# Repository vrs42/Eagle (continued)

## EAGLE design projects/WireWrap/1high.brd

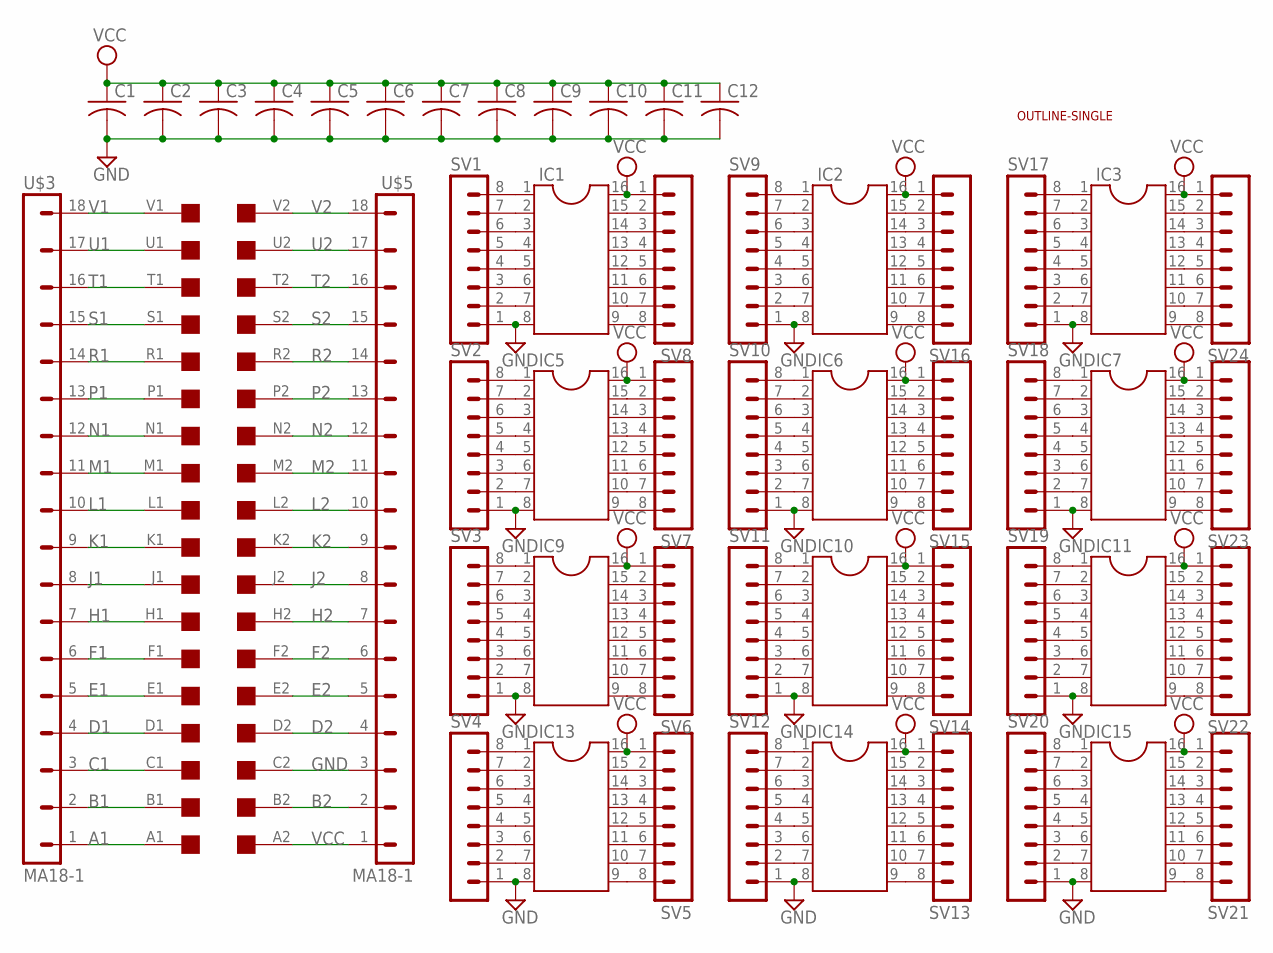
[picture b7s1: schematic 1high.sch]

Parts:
C1, C2, C3, C4, C5, C6, C7, C8, C9, C10, C11, C12: C-US050-025X075; C050-025X075
IC1, IC2, IC3, IC5, IC6, IC7, IC9, IC10, IC11, IC13, IC14, IC15: DIL16
SV1, SV2, SV3, SV4, SV5, SV6, SV7, SV8, SV9, SV10, SV11, SV12, SV13, SV14, SV15, SV16, SV17, SV18, SV19, SV20, SV21, SV22, SV23, SV24: MA08-1
U$2: OUTLINE-SINGLE; SINGLE
U$3, U$5: MA18-1
U$4: EDGE-2CONNECTOR; EDGE-CON2

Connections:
A1: U$3.1, U$4.A1
B1: U$3.2, U$4.B1
B2: U$4.B2, U$5.2
C1: U$3.3, U$4.C1
D1: U$3.4, U$4.D1
D2: U$4.D2, U$5.4
E1: U$3.5, U$4.E1
E2: U$4.E2, U$5.5
F1: U$3.6, U$4.F1
F2: U$4.F2, U$5.6
GND: C1.2, C2.2, C3.2, C4.2, C5.2, C6.2, C7.2, C8.2, C9.2, C10.2, C11.2, C12.2, IC1.8, IC2.8, IC3.8, IC5.8, IC6.8, IC7.8, IC9.8, IC10.8, IC11.8, IC13.8, IC14.8, IC15.8, SV1.1, SV2.1, SV3.1, SV4.1, SV9.1, SV10.1, SV11.1, SV12.1, SV17.1, SV18.1, SV19.1, SV20.1, U$4.C2, U$5.3
H1: U$3.7, U$4.H1
H2: U$4.H2, U$5.7
J1: U$3.8, U$4.J1
J2: U$4.J2, U$5.8
K1: U$3.9, U$4.K1
K2: U$4.K2, U$5.9
L1: U$3.10, U$4.L1
L2: U$4.L2, U$5.10
M1: U$3.11, U$4.M1
M2: U$4.M2, U$5.11
N1: U$3.12, U$4.N1
N2: U$4.N2, U$5.12
unnamed: IC1.7, SV1.2
unnamed: IC1.6, SV1.3
unnamed: IC1.5, SV1.4
unnamed: IC1.4, SV1.5
unnamed: IC1.3, SV1.6
unnamed: IC1.2, SV1.7
unnamed: IC1.1, SV1.8
unnamed: IC5.7, SV2.2
unnamed: IC5.6, SV2.3
unnamed: IC5.5, SV2.4
unnamed: IC5.4, SV2.5
unnamed: IC5.3, SV2.6
unnamed: IC5.2, SV2.7
unnamed: IC5.1, SV2.8
unnamed: IC9.7, SV3.2
unnamed: IC9.6, SV3.3
unnamed: IC9.5, SV3.4
unnamed: IC9.4, SV3.5
unnamed: IC9.3, SV3.6
unnamed: IC9.2, SV3.7
unnamed: IC9.1, SV3.8
unnamed: IC13.7, SV4.2
unnamed: IC13.6, SV4.3
unnamed: IC13.5, SV4.4
unnamed: IC13.4, SV4.5
unnamed: IC13.3, SV4.6
unnamed: IC13.2, SV4.7
unnamed: IC13.1, SV4.8
unnamed: IC2.1, SV9.8
unnamed: IC2.2, SV9.7
unnamed: IC2.3, SV9.6
unnamed: IC2.4, SV9.5
unnamed: IC2.5, SV9.4
unnamed: IC2.6, SV9.3
unnamed: IC2.7, SV9.2
unnamed: IC6.1, SV10.8
unnamed: IC6.2, SV10.7
unnamed: IC6.3, SV10.6
unnamed: IC6.4, SV10.5
unnamed: IC6.5, SV10.4
unnamed: IC6.6, SV10.3
unnamed: IC6.7, SV10.2
unnamed: IC10.1, SV11.8
unnamed: IC10.2, SV11.7
unnamed: IC10.3, SV11.6
unnamed: IC10.4, SV11.5
unnamed: IC10.5, SV11.4
unnamed: IC10.6, SV11.3
unnamed: IC10.7, SV11.2
unnamed: IC14.1, SV12.8
unnamed: IC14.2, SV12.7
unnamed: IC14.3, SV12.6
unnamed: IC14.4, SV12.5
unnamed: IC14.5, SV12.4
unnamed: IC14.6, SV12.3
unnamed: IC14.7, SV12.2
unnamed: IC6.15, SV15.2
unnamed: IC6.14, SV15.3
unnamed: IC6.13, SV15.4
unnamed: IC6.12, SV15.5
unnamed: IC6.11, SV15.6
unnamed: IC6.10, SV15.7
unnamed: IC6.9, SV15.8
unnamed: IC10.15, SV14.2
unnamed: IC10.14, SV14.3
unnamed: IC10.13, SV14.4
unnamed: IC10.12, SV14.5
unnamed: IC10.11, SV14.6
unnamed: IC10.10, SV14.7
unnamed: IC10.9, SV14.8
unnamed: IC1.9, SV8.8
unnamed: IC1.10, SV8.7
unnamed: IC1.11, SV8.6
unnamed: IC1.12, SV8.5
unnamed: IC1.13, SV8.4
unnamed: IC1.14, SV8.3
unnamed: IC1.15, SV8.2
unnamed: IC5.9, SV7.8
unnamed: IC5.10, SV7.7
unnamed: IC5.11, SV7.6
unnamed: IC5.12, SV7.5
unnamed: IC5.13, SV7.4
unnamed: IC5.14, SV7.3
unnamed: IC5.15, SV7.2
unnamed: IC2.15, SV16.2
unnamed: IC2.14, SV16.3
unnamed: IC2.13, SV16.4
unnamed: IC2.12, SV16.5
unnamed: IC2.11, SV16.6
unnamed: IC2.10, SV16.7
unnamed: IC2.9, SV16.8
unnamed: IC13.15, SV5.2
unnamed: IC13.14, SV5.3
unnamed: IC13.13, SV5.4
unnamed: IC13.12, SV5.5
unnamed: IC13.11, SV5.6
unnamed: IC13.10, SV5.7
unnamed: IC13.9, SV5.8
unnamed: IC9.15, SV6.2
unnamed: IC9.14, SV6.3
unnamed: IC9.13, SV6.4
unnamed: IC9.12, SV6.5
unnamed: IC9.11, SV6.6
unnamed: IC9.10, SV6.7
unnamed: IC9.9, SV6.8
unnamed: IC14.15, SV13.2
unnamed: IC14.14, SV13.3
unnamed: IC14.13, SV13.4
unnamed: IC14.12, SV13.5
unnamed: IC14.11, SV13.6
unnamed: IC14.10, SV13.7
unnamed: IC14.9, SV13.8
unnamed: IC3.7, SV17.2
unnamed: IC3.6, SV17.3
unnamed: IC3.5, SV17.4
unnamed: IC3.4, SV17.5
unnamed: IC3.3, SV17.6
unnamed: IC3.2, SV17.7
unnamed: IC3.1, SV17.8
unnamed: IC7.7, SV18.2
unnamed: IC7.6, SV18.3
unnamed: IC7.5, SV18.4
unnamed: IC7.4, SV18.5
unnamed: IC7.3, SV18.6
unnamed: IC7.2, SV18.7
unnamed: IC7.1, SV18.8
unnamed: IC11.7, SV19.2
unnamed: IC11.6, SV19.3
unnamed: IC11.5, SV19.4
unnamed: IC11.4, SV19.5
unnamed: IC11.3, SV19.6
unnamed: IC11.2, SV19.7
unnamed: IC11.1, SV19.8
unnamed: IC15.7, SV20.2
unnamed: IC15.6, SV20.3
unnamed: IC15.5, SV20.4
unnamed: IC15.4, SV20.5
unnamed: IC15.3, SV20.6
unnamed: IC15.2, SV20.7
unnamed: IC15.1, SV20.8
unnamed: IC15.15, SV21.2
unnamed: IC15.14, SV21.3
unnamed: IC15.13, SV21.4
unnamed: IC15.12, SV21.5
unnamed: IC15.11, SV21.6
unnamed: IC15.10, SV21.7
unnamed: IC15.9, SV21.8
unnamed: IC11.15, SV22.2
unnamed: IC11.14, SV22.3
unnamed: IC11.13, SV22.4
unnamed: IC11.12, SV22.5
unnamed: IC11.11, SV22.6
unnamed: IC11.10, SV22.7
unnamed: IC11.9, SV22.8
unnamed: IC7.15, SV23.2
unnamed: IC7.14, SV23.3
unnamed: IC7.13, SV23.4
unnamed: IC7.12, SV23.5
unnamed: IC7.11, SV23.6
unnamed: IC7.10, SV23.7
unnamed: IC7.9, SV23.8
unnamed: IC3.15, SV24.2
unnamed: IC3.14, SV24.3
unnamed: IC3.13, SV24.4
unnamed: IC3.12, SV24.5
unnamed: IC3.11, SV24.6
unnamed: IC3.10, SV24.7
unnamed: IC3.9, SV24.8
P1: U$3.13, U$4.P1
P2: U$4.P2, U$5.13
R1: U$3.14, U$4.R1
R2: U$4.R2, U$5.14
S1: U$3.15, U$4.S1
S2: U$4.S2, U$5.15
T1: U$3.16, U$4.T1
T2: U$4.T2, U$5.16
U1: U$3.17, U$4.U1
U2: U$4.U2, U$5.17
V1: U$3.18, U$4.V1
V2: U$4.V2, U$5.18
VCC: C1.1, C2.1, C3.1, C4.1, C5.1, C6.1, C7.1, C8.1, C9.1, C10.1, C11.1, C12.1, IC1.16, IC2.16, IC3.16, IC5.16, IC6.16, IC7.16, IC9.16, IC10.16, IC11.16, IC13.16, IC14.16, IC15.16, SV5.1, SV6.1, SV7.1, SV8.1, SV13.1, SV14.1, SV15.1, SV16.1, SV21.1, SV22.1, SV23.1, SV24.1, U$4.A2, U$5.1

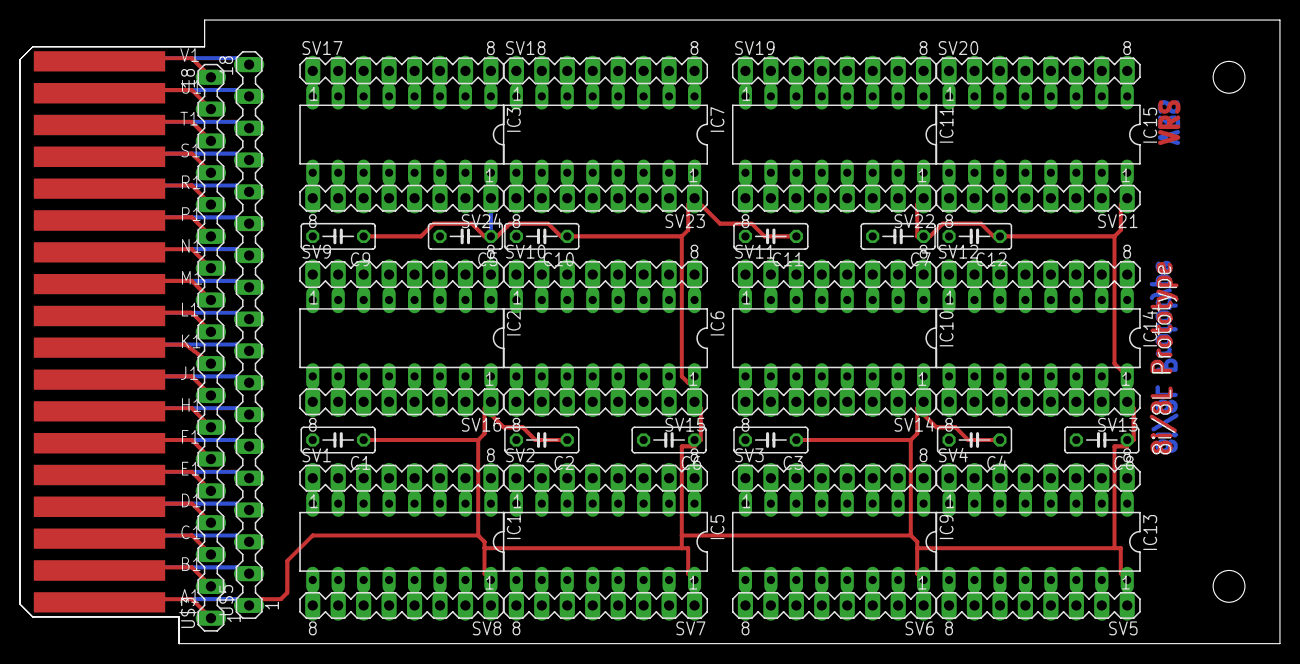
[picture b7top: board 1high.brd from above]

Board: 2 copper layers, 125.7 x 62.2 mm, 52 parts (0 on the bottom side), 204 nets.
